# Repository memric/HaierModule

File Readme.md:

# Haire Module

KiCad Remote Control module project for Haier air conditioner.

Based on Espressif [ESP32-C3-WROOM-02](https://www.espressif.com/sites/default/files/documentation/esp32-c3-wroom-02_datasheet_en.pdf)

[Telegram bot based firmware](https://github.com/memric/HaierModuleFirmware) can be used.

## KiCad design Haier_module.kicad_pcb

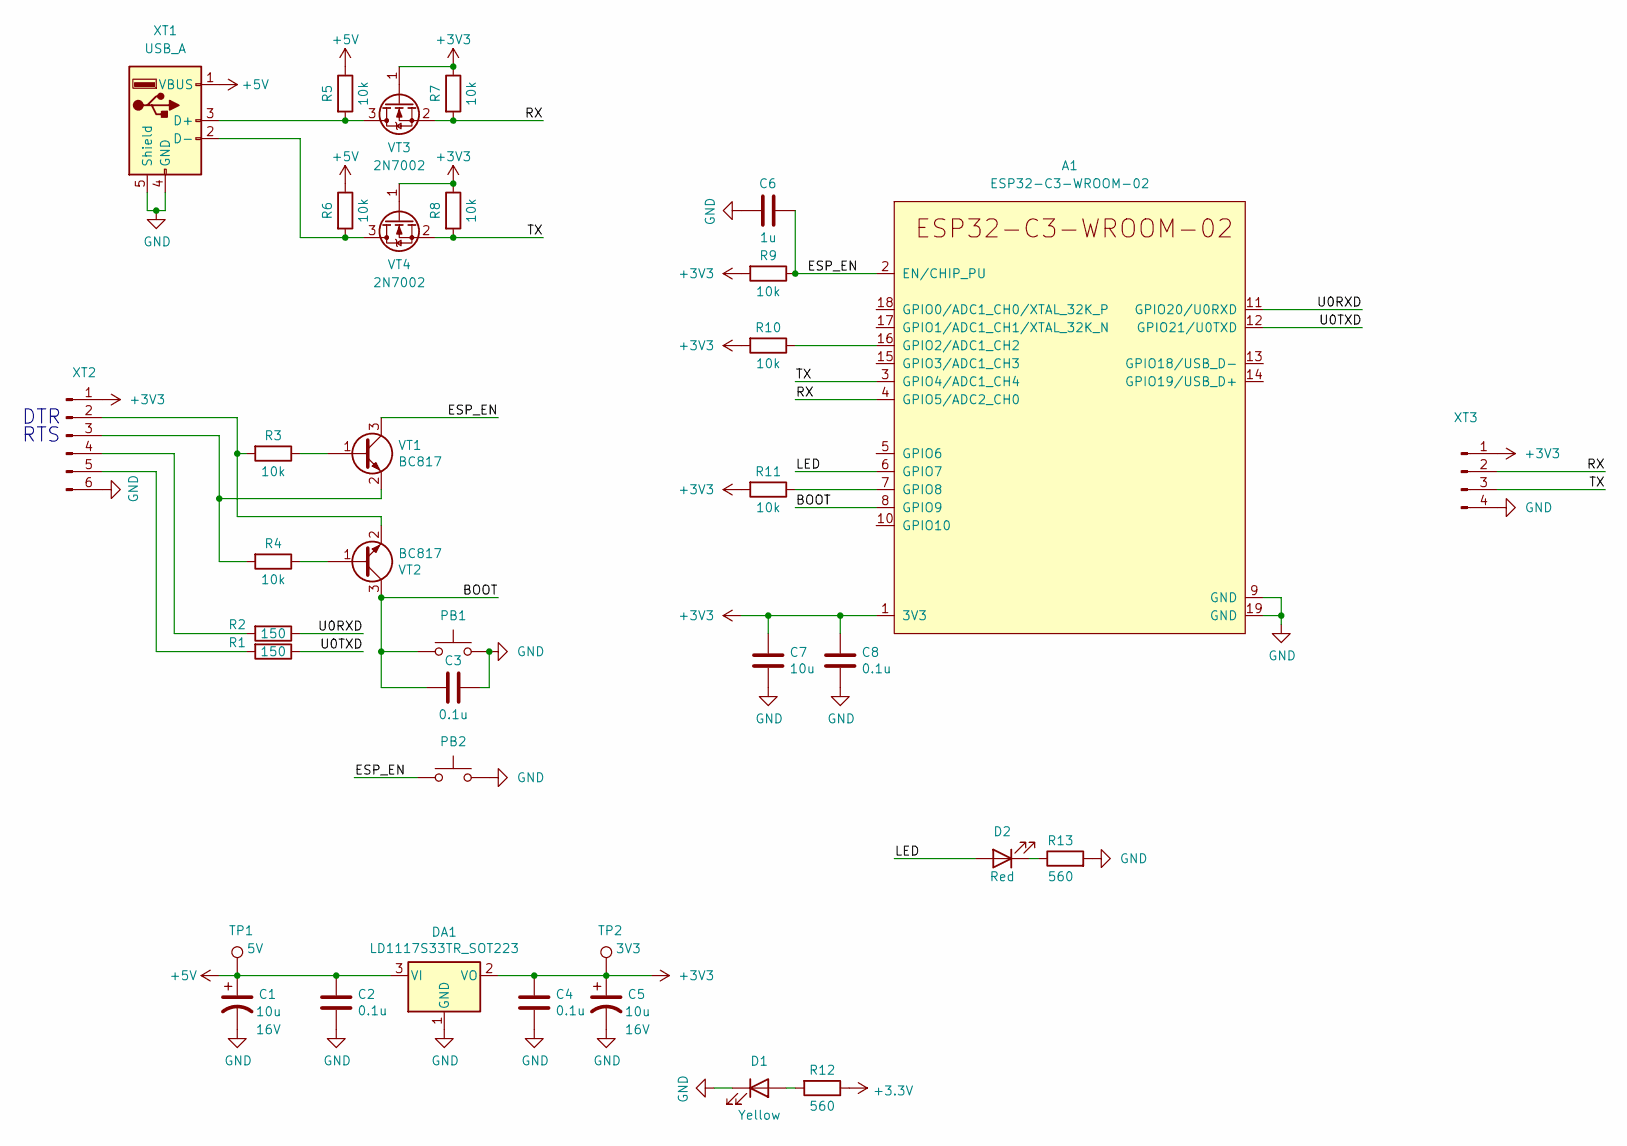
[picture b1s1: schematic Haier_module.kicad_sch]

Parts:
A1: ESP32-C3-WROOM-02
C1, C5: 10u; CP_EIA-3216-18_Kemet-A; Voltage 16V
C2, C3, C4, C8: 0.1u; C_0603_1608Metric
C6: 1u; C_0603_1608Metric
C7: 10u; C_0805_2012Metric
D1: Yellow; LED_0805_2012Metric_Pad1.15x1.40mm_HandSolder
D2: Red; LED_0805_2012Metric_Pad1.15x1.40mm_HandSolder
DA1: LD1117S33TR_SOT223; SOT-223-3_TabPin2
PB1, PB2: PartNumber B3U1000P
R1, R2: 150; R_0603_1608Metric; Tolerance 5
R3, R4, R5, R6, R7, R8, R9, R10, R11: 10k; R_0603_1608Metric; Tolerance 5
R12: 560; R_0603_1608Metric
R13: 560; R_0603_1608Metric; Tolerance 5%
TP1: 5V; TestPoint_Pad_D1.5mm
TP2: 3V3; TestPoint_Pad_D1.5mm
VT1, VT2: BC817; SOT-23
VT3, VT4: 2N7002; SOT-23
XT1: USB_A; L-KLS1-180A-W
XT2, XT3: (no value)

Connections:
+5V: C1.1, C2.1, DA1.3 (VI), R5.1, R6.1, TP1.1, XT1.1 (VBUS)
/BOOT: A1.8 (GPIO9), C3.1, PB1.1, VT2.3 (C)
/ESP_EN: A1.2 (EN/CHIP_PU), C6.2, PB2.1, R9.1, VT1.3 (C)
/LED: A1.6 (GPIO7), D2.2 (A)
/RX: A1.4 (GPIO5/ADC2_CH0), R7.2, VT3.2 (S), XT3.2
/TX: A1.3 (GPIO4/ADC1_CH4), R8.2, VT4.2 (S), XT3.3
/U0RXD: A1.11 (GPIO20/U0RXD), R2.1
/U0TXD: A1.12 (GPIO21/U0TXD), R1.1
GND: A1.9 (GND), A1.19 (GND), C1.2, C2.2, C3.2, C4.2, C5.2, C6.1, C7.2, C8.2, D1.1 (K), DA1.1 (GND), PB1.2, PB2.2, R13.2, XT1.4 (GND), XT1.5 (Shield), XT2.6, XT3.4
unnamed: A1.7 (GPIO8), R11.1
unnamed: A1.16 (GPIO2/ADC1_CH2), R10.1
unnamed: D1.2 (A), R12.2
unnamed: D2.1 (K), R13.1
unnamed: R1.2, XT2.5
unnamed: R2.2, XT2.4
unnamed: R3.1, VT1.1 (B)
unnamed: R3.2, VT2.2 (E), XT2.2
unnamed: R4.1, VT2.1 (B)
unnamed: R4.2, VT1.2 (E), XT2.3
unnamed: R5.2, VT3.3 (D), XT1.3 (D+)
unnamed: R6.2, VT4.3 (D), XT1.2 (D-)

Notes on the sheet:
DTR
RTS

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
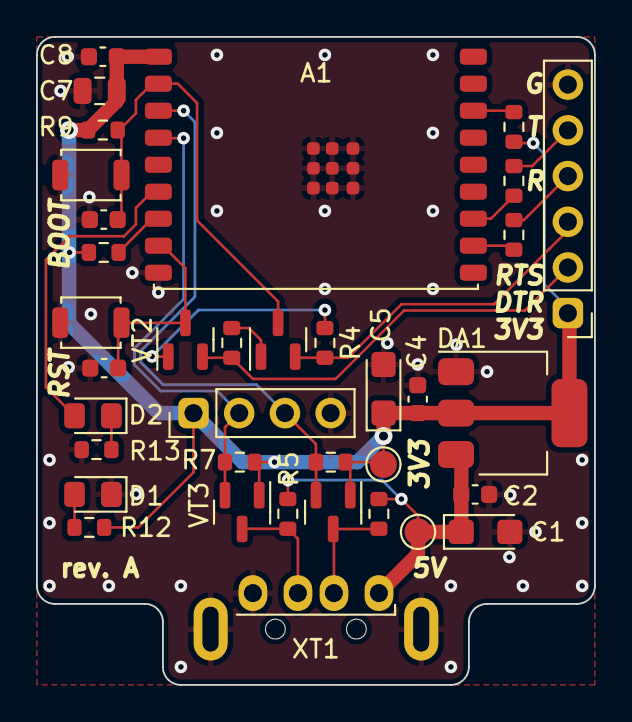
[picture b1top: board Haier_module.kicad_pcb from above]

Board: 2 copper layers, 31.0 x 36.0 mm, 36 parts (0 on the bottom side), 22 nets.

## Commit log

2025-07-19 Init
2025-07-19 Add Readme
